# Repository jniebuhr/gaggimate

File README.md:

<p align="center">

<br />

[![CC BY-NC-SA 4.0][cc-by-nc-sa-shield]][cc-by-nc-sa]
[![Sonar QG][sonar-shield]][sonar-url]
[![Sonar Violations][sonar-violations]][sonar-url]
[![Sonar Tech Debt][sonar-tech-debt]][sonar-url]

</p>

This project upgrades a Gaggia espresso machine with smart controls to improve your coffee-making experience. By adding a display and custom electronics, you can monitor and control the machine more easily.

## Features

- **Temperature Control**: Monitor the boiler temperature to ensure optimal brewing conditions.
- **Brew timer**: Set a target duration and run the brewing for the specific time.
- **Steam and Hot Water mode**: Control the pump and valve to run the respective task.
- **Safety Features**: Automatic shutoff if the system becomes unresponsive or overheats.
- **User Interface**: Simple, intuitive display to control and monitor the machine.

## Screenshots and Images

### How to buy

You can buy your kit on https://shop.gaggimate.eu/

## How It Works

The display allows you to control the espresso machine and see live temperature updates. If the machine becomes unresponsive or the temperature goes too high, it will automatically turn off for safety.

## Docs

The docs were moved to [https://gaggimate.eu/](https://gaggimate.eu/). You can find all sourcing and assembly information there.
Additional documentation for the WebSocket API can be found in [docs/websocket-api.yaml](docs/websocket-api.yaml).

## Hardware Files

The hardware files were moved to [gaggimate/parts](https://github.com/gaggimate/parts).

## License

This work is licensed under CC BY-NC-SA 4.0. To view a copy of this license, visit https://creativecommons.org/licenses/by-nc-sa/4.0/

[sonar-violations]: https://img.shields.io/sonar/blocker_violations/jniebuhr_gaggimate?server=https%3A%2F%2Fsonarcloud.io&style=for-the-badge
[sonar-shield]: https://img.shields.io/sonar/quality_gate/jniebuhr_gaggimate?server=https%3A%2F%2Fsonarcloud.io&style=for-the-badge
[sonar-tech-debt]: https://img.shields.io/sonar/tech_debt/jniebuhr_gaggimate?server=https%3A%2F%2Fsonarcloud.io&style=for-the-badge
[sonar-url]: https://sonarcloud.io/project/overview?id=jniebuhr_gaggimate
[cc-by-nc-sa]: http://creativecommons.org/licenses/by-nc-sa/4.0/
[cc-by-nc-sa-image]: https://licensebuttons.net/l/by-nc-sa/4.0/88x31.png
[cc-by-nc-sa-shield]: https://img.shields.io/badge/License-CC%20BY--NC--SA%204.0-lightgrey.svg?style=for-the-badge

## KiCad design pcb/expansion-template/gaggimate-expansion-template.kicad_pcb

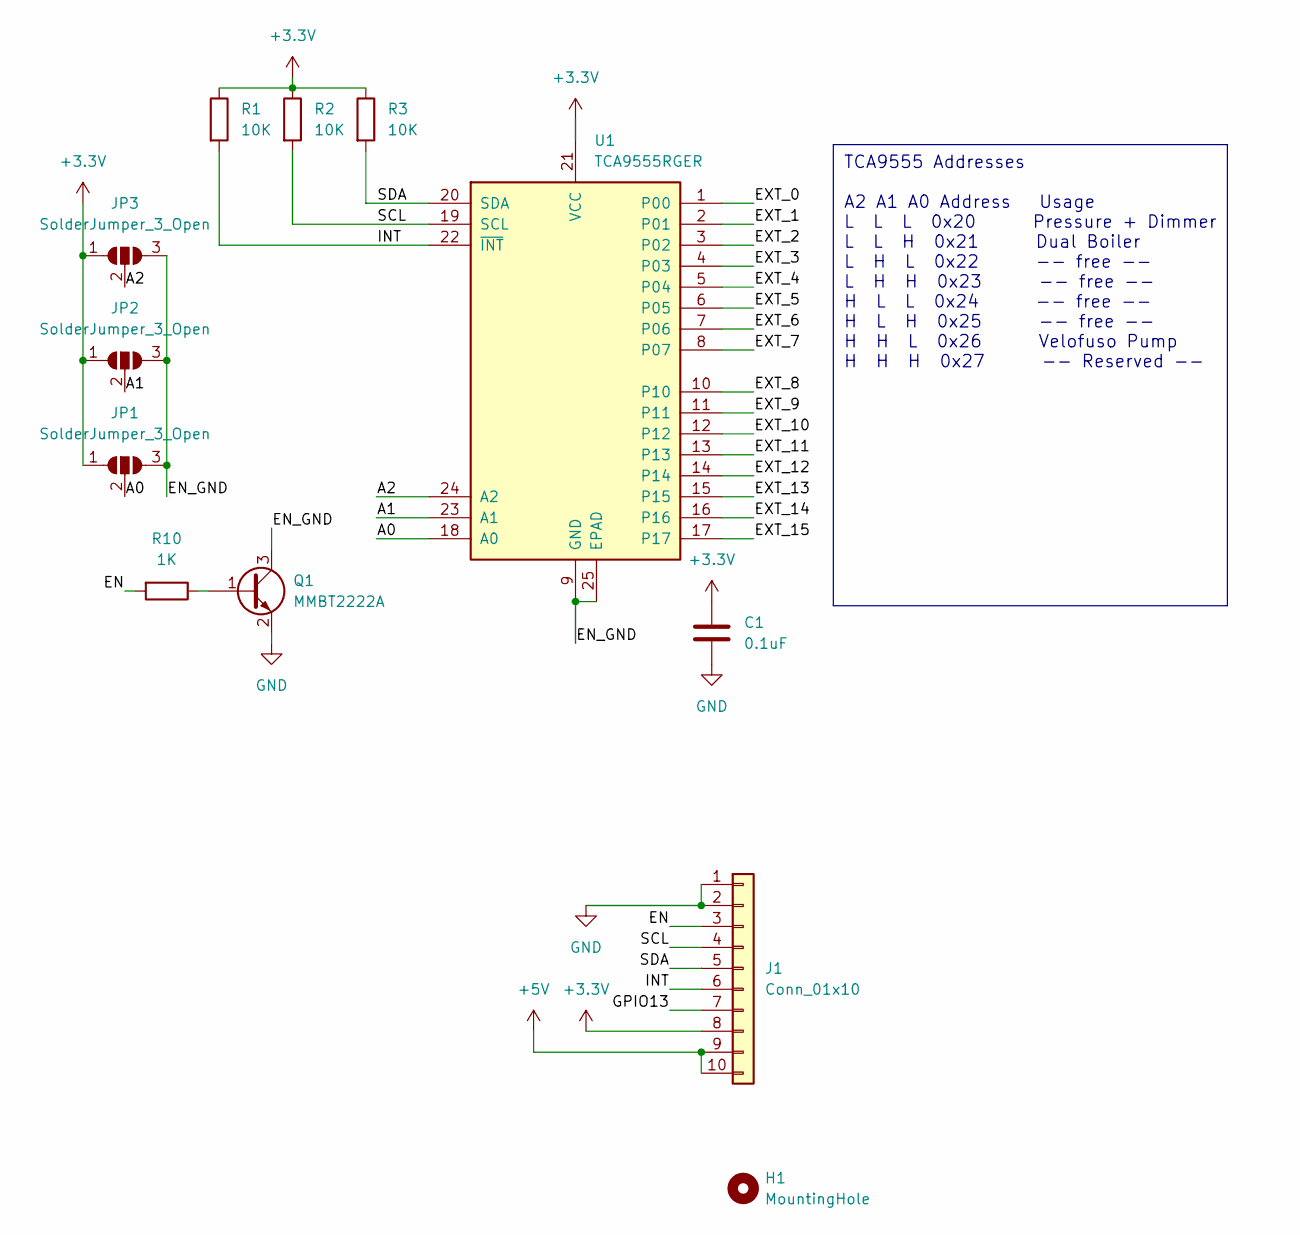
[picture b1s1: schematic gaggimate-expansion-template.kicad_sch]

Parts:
C1: 0.1uF; C_0603_1608Metric
H1: MountingHole; MountingHole_2.7mm_M2.5
J1: Conn_01x10; PinSocket_1x10_P2.54mm_Vertical
JP1, JP2, JP3: SolderJumper_3_Open; SolderJumper-3_P1.3mm_Open_RoundedPad1.0x1.5mm
Q1: MMBT2222A; SOT-23
R1, R2, R3: 10K; R_0603_1608Metric
R10: 1K; R_0603_1608Metric
U1: TCA9555RGER; VQFN-24-1EP_4x4mm_P0.5mm_EP2.45x2.45mm

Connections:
+3.3V: C1.1, J1.8, JP1.1 (A), JP2.1 (A), JP3.1 (A), R1.1, R2.1, R3.1, U1.21 (VCC)
+5V: J1.9, J1.10
/A0: JP1.2 (C), U1.18 (A0)
/A1: JP2.2 (C), U1.23 (A1)
/A2: JP3.2 (C), U1.24 (A2)
/EN: J1.3, R10.2
/EN_GND: JP1.3 (B), JP2.3 (B), JP3.3 (B), Q1.3 (C), U1.9 (GND), U1.25 (EPAD)
/EXT_0: U1.1 (P00)
/EXT_1: U1.2 (P01)
/EXT_2: U1.3 (P02)
/EXT_3: U1.4 (P03)
/EXT_4: U1.5 (P04)
/EXT_5: U1.6 (P05)
/EXT_6: U1.7 (P06)
/EXT_7: U1.8 (P07)
/EXT_8: U1.10
/EXT_9: U1.11
/EXT_10: U1.12
/EXT_11: U1.13
/EXT_12: U1.14
/EXT_13: U1.15
/EXT_14: U1.16
/EXT_15: U1.17
/GPIO13: J1.7
/INT: J1.6, R1.2, U1.22 (~INT)
/SCL: J1.4, R2.2, U1.19 (SCL)
/SDA: J1.5, R3.2, U1.20 (SDA)
GND: C1.2, J1.1, J1.2, Q1.2 (E)
unnamed: Q1.1 (B), R10.1

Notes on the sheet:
TCA9555 Addresses A2 A1 A0 Address Usage L L L 0x20 Pressure + Dimmer L L H 0x21 Dual Boiler L H L 0x22 -- free -- L H H 0x23 -- free -- H L L 0x24 -- free -- H L H 0x25 -- free -- H H L 0x26 Velofuso Pump H H H 0x27 -- Reserved --

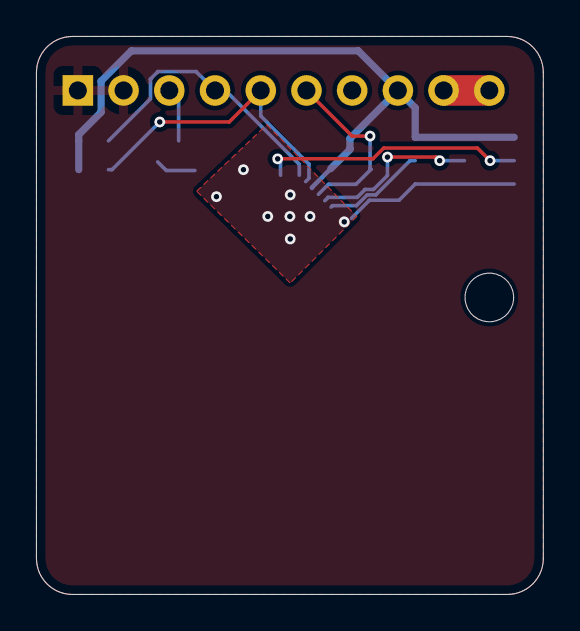
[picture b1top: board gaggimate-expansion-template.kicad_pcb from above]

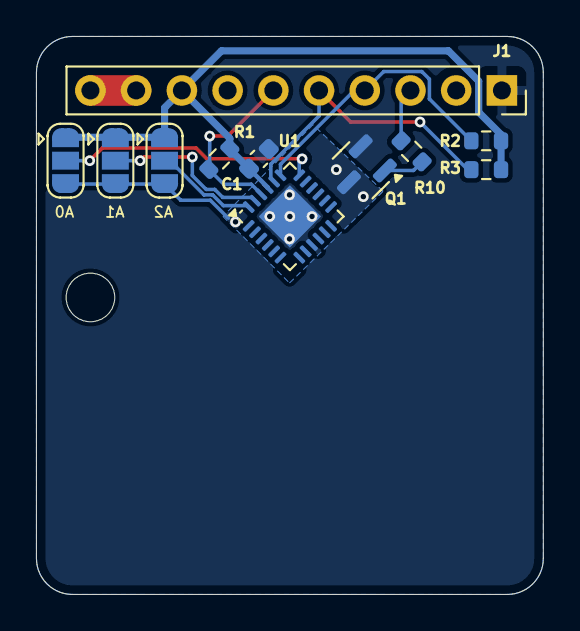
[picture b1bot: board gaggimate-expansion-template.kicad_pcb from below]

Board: 2 copper layers, 28.2 x 31.0 mm, 12 parts (11 on the bottom side), 12 nets.

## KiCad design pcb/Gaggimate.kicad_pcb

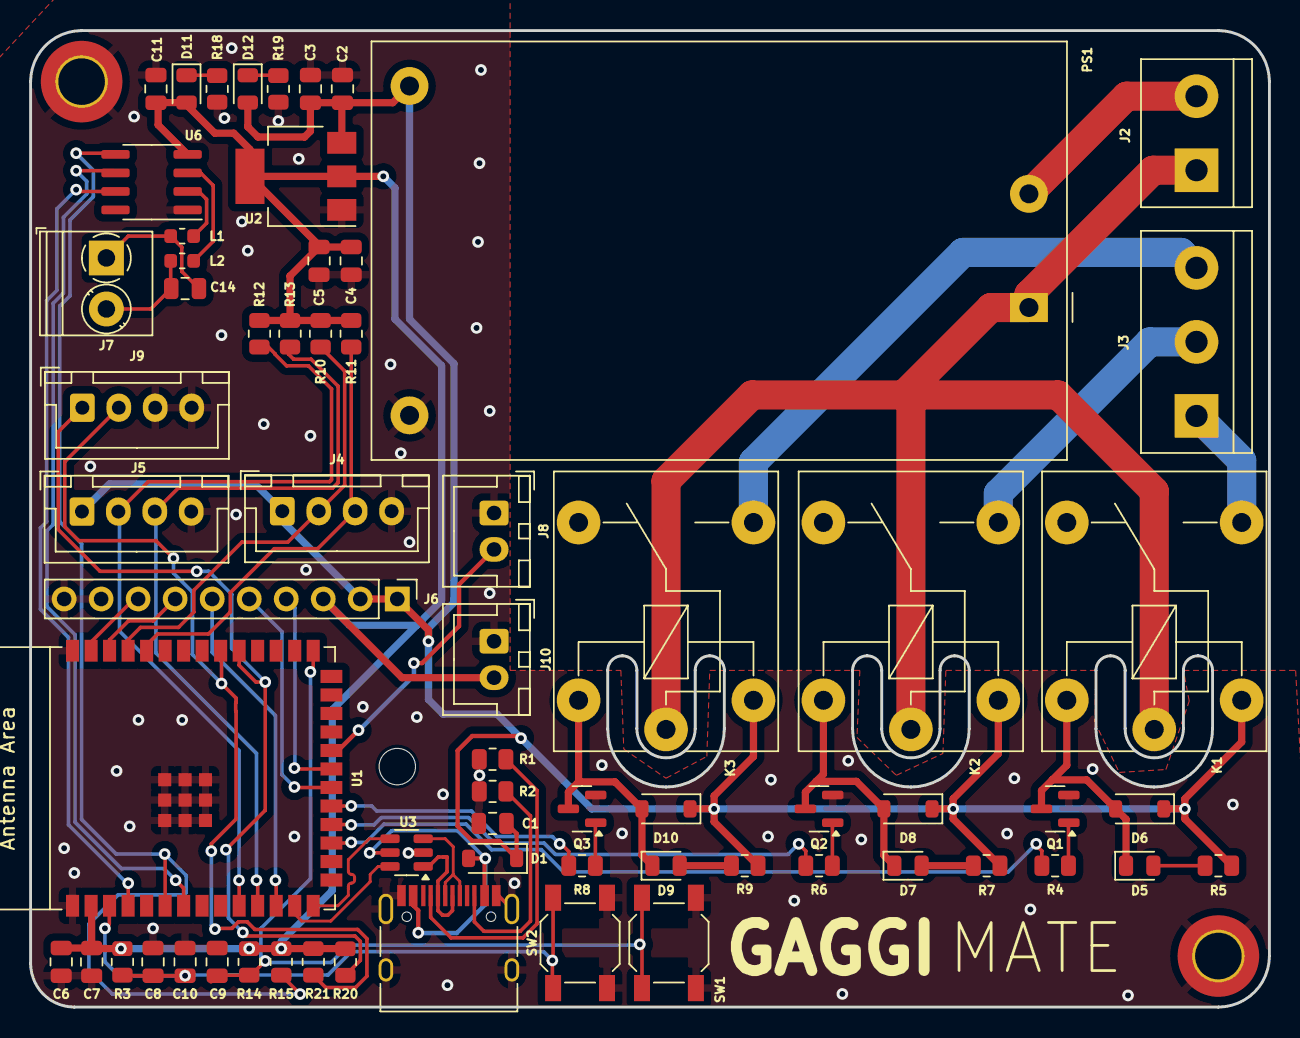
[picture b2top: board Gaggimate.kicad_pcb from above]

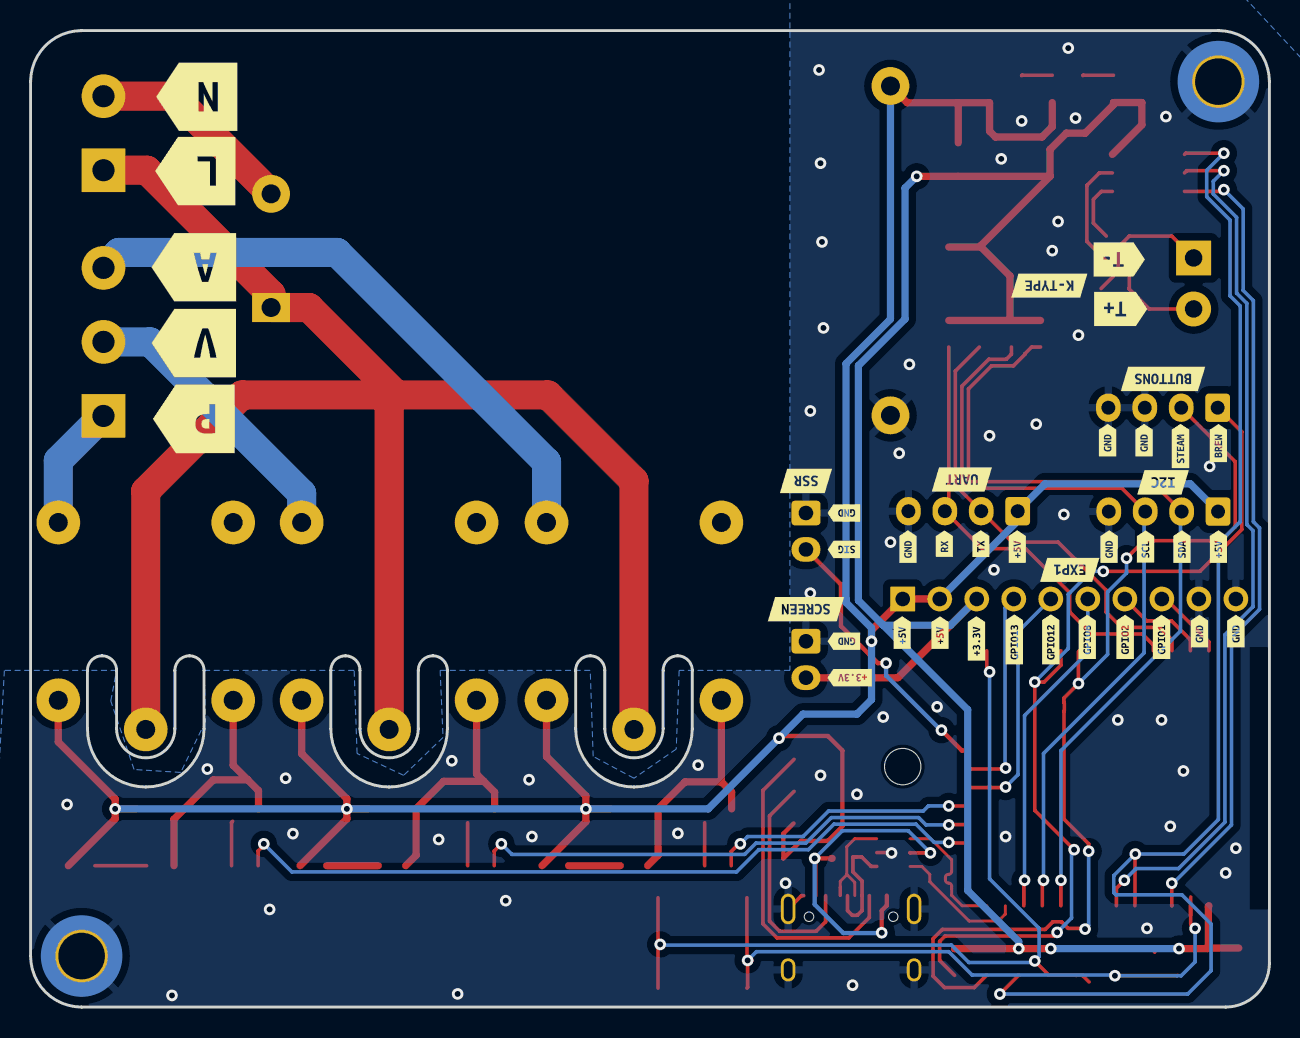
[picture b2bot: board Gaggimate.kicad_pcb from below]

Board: 2 copper layers, 85.0 x 67.0 mm, 107 parts (40 on the bottom side), 50 nets.

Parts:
C1, C2, C6: 10uF; C_0805_2012Metric
C3, C5, C7, C9, C10: 0.1uF; C_0805_2012Metric
C4: 22uF; C_0805_2012Metric
C8, C11: 1uF; C_0805_2012Metric
C14: 10nF; C_0805_2012Metric
D1: 1N5819; D_SOD-123
D5, D7, D9, D11, D12: LED; LED_0805_2012Metric
D6, D8, D10: 1N4148W; D_SOD-123
H1, H1#2: MountingHole_Pad; MountingHole_3.2mm_M3_DIN965_Pad_TopBottom
J1: USB_C_Receptacle; USB_C_Receptacle_HRO_TYPE-C-31-M-12
J2: Conn_01x02; TerminalBlock_bornier-2_P5.08mm
J3: Conn_01x03; TerminalBlock_bornier-3_P5.08mm
J4, J5, J9: Conn_01x04; JST_XH_B4B-XH-A_1x04_P2.50mm_Vertical
J6: Conn_01x10; PinHeader_1x10_P2.54mm_Vertical
J7: Conn_01x02; TerminalBlock_Phoenix_PT-1,5-2-3.5-H_1x02_P3.50mm_Horizontal
J8, J10: Conn_01x02; JST_XH_B2B-XH-A_1x02_P2.50mm_Vertical
K1, K2, K3: Relay_SPDT; Relay_SPDT_Finder_36.11
L1, L2: 470R; L_0603_1608Metric
PS1: HLK-10M05; Converter_ACDC_HiLink_HLK-10Mxx
Q1, Q2, Q3: MMBT2222A; SOT-23
R1, R2: 5.1K; R_0805_2012Metric
R3, R10, R11, R12, R13, R14, R15, R20, R21: 10K; R_0805_2012Metric
R4, R6, R8: 1K; R_0805_2012Metric
R5, R7, R9, R19: 150R; R_0805_2012Metric
R18: 68R; R_0805_2012Metric
SW1, SW2: SW_Push; SW_SPST_SKQG_WithStem
U1: ESP32-S3-WROOM-1
U2: AMS1117-3.3; SOT-223-3_TabPin2
U3: USBLC6-2SC6; SOT-23-6
U6: MAX31855EASA; SOIC-8_3.9x4.9mm_P1.27mm
kibuzzard-6735A9F6: G***; kibuzzard-6735A9F6
kibuzzard-6735A9FB: G***; kibuzzard-6735A9FB
kibuzzard-67411A55: G***; kibuzzard-67411A55
kibuzzard-673226A0: G***; kibuzzard-673226A0
kibuzzard-673226A8: G***; kibuzzard-673226A8
kibuzzard-673226AF, kibuzzard-673226AF#2: G***; kibuzzard-673226AF
kibuzzard-673226B7: G***; kibuzzard-673226B7
kibuzzard-673226BE: G***; kibuzzard-673226BE
kibuzzard-673226D2: G***; kibuzzard-673226D2
kibuzzard-6732257B: G***; kibuzzard-6732257B
kibuzzard-6732261A: G***; kibuzzard-6732261A
kibuzzard-6732266F: G***; kibuzzard-6732266F
kibuzzard-6732270D: G***; kibuzzard-6732270D
kibuzzard-6732274F: G***; kibuzzard-6732274F
kibuzzard-6732277B: G***; kibuzzard-6732277B
kibuzzard-6732278E: G***; kibuzzard-6732278E
kibuzzard-6732279D: G***; kibuzzard-6732279D
kibuzzard-67322575: G***; kibuzzard-67322575
kibuzzard-67322649, kibuzzard-67322649#2, kibuzzard-67322649#3, kibuzzard-67322649#4, kibuzzard-67322649#5, kibuzzard-67322649#6, kibuzzard-67322649#7, kibuzzard-67322649#8: G***; kibuzzard-67322649
kibuzzard-67322650, kibuzzard-67322650#2, kibuzzard-67322650#3, kibuzzard-67322650#4: G***; kibuzzard-67322650
kibuzzard-67322655: G***; kibuzzard-67322655
kibuzzard-67322681: G***; kibuzzard-67322681
kibuzzard-67322686: G***; kibuzzard-67322686
kibuzzard-67322714: G***; kibuzzard-67322714
kibuzzard-67322749: G***; kibuzzard-67322749
kibuzzard-67322755: G***; kibuzzard-67322755
kibuzzard-67322768: G***; kibuzzard-67322768
kibuzzard-67322783: G***; kibuzzard-67322783
kibuzzard-67322833: G***; kibuzzard-67322833

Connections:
+3.3V: C4.1, C5.1, C6.1, C7.1, C11.1, D11.2 (A), J6.3, J10.2, R3.1, R10.1, R11.1, R12.1, R13.1, R14.1, R15.1, R20.1, R21.1, U1.2 (3V3), U2.2 (VO), U6.4 (V_CC)
+5V: C1.1, C2.1, C3.1, D1.1 (K), D6.1 (K), D8.1 (K), D10.1 (K), D12.2 (A), J4.1, J5.1, J6.1, J6.2, K1.A1, K2.A1, K3.A1, PS1.4 (+Vout), R5.2, R7.2, R9.2, U2.3 (VI)
/BOOT: C9.1, R14.2, SW1.2, U1.27 (GPIO0/BOOT)
/BTN_BREW: J9.1, R20.2, U1.31 (GPIO38/FSPIWP/SUBSPIWP)
/BTN_STEAM: J9.2, R21.2, U1.32 (MTCK/GPIO39/CLK_OUT3/SUBSPICS1)
/CHIP_PU: C8.1, C10.1, R3.2, SW2.2, U1.3 (EN)
/GPIO1: J6.8, U1.39 (GPIO1/TOUCH1/ADC1_CH0)
/GPIO2: J6.7, U1.38 (GPIO2/TOUCH2/ADC1_CH1)
/GPIO8: J6.6, U1.12 (GPIO8/TOUCH8/ADC1_CH7/SUBSPICS1)
/GPIO12: J6.5, U1.20 (GPIO12/TOUCH12/ADC2_CH1/FSPICLK/FSPIIO6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)
/GPIO13: J6.4, U1.21 (GPIO13/TOUCH13/ADC2_CH2/FSPIQ/FSPIIO7/S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)
/LINE_GRINDER: J3.3, K3.14
/LINE_PUMP: J3.1, K1.14
/LINE_VALVE: J3.2, K2.14
/MAX_CS: U1.7 (GPIO7/TOUCH7/ADC1_CH6), U6.6 (~CS)
/RELAY_GRINDER: R8.2, U1.19 (GPIO11/TOUCH11/ADC2_CH0/FSPID/FSPIIO5/S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)
/RELAY_PUMP: R4.2, U1.17 (GPIO9/TOUCH9/ADC1_CH8/FSPIHD/SUBSPIHD)
/RELAY_VALVE: R6.2, U1.18 (GPIO10/TOUCH10/ADC1_CH9/FSPICS0/FSPIIO4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)
/SCL: J5.2, R12.2, U1.10 (GPIO17/U1TXD/ADC2_CH6)
/SDA: J5.3, R13.2, U1.11 (GPIO18/U1RXD/ADC2_CH7/CLK_OUT3)
/SPI_CLK: R15.2, U1.6 (GPIO6/TOUCH6/ADC1_CH5), U6.5 (SCK)
/SPI_MISO: U1.4 (GPIO4/TOUCH4/ADC1_CH3), U6.7 (SO)
/SSR: J8.2, U1.22 (GPIO14/TOUCH14/ADC2_CH3/FSPIWP/FSPIDQS/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)
/UART_RX0: J4.3, R11.2, U1.36 (U0RXD/GPIO44/CLK_OUT2)
/UART_TX0: J4.2, R10.2, U1.37 (U0TXD/GPIO43/CLK_OUT1)
/USB_DN: U1.13 (GPIO19/U1RTS/ADC2_CH8/CLK_OUT2/USB_D-), U3.6 (I/O1)
/USB_DP: U1.14 (GPIO20/U1CTS/ADC2_CH9/CLK_OUT1/USB_D+), U3.4 (I/O2)
/USB_UF_DN: J1.A7 (D-), J1.B7 (D-), U3.1 (I/O1)
/USB_UF_DP: J1.A6 (D+), J1.B6 (D+), U3.3 (I/O2)
GND: C1.2, C2.2, C3.2, C4.2, C5.2, C6.2, C7.2, C8.2, C9.2, C10.2, C11.2, H1.1, H1#2.1, J1.A1 (GND), J1.A12 (GND), J1.B1 (GND), J1.B12 (GND), J1.S1 (SHIELD), J4.4, J5.4, J6.9, J6.10, J8.1, J9.3, J9.4, J10.1, PS1.3 (-Vout), Q1.2 (E), Q2.2 (E), Q3.2 (E), R1.1, R2.1, R18.2, R19.2, SW1.1, SW2.1, U1.1 (GND), U1.40 (GND), U1.41 (GND), U2.1 (GND), U3.2 (GND), U6.1 (GND)
LINE: J2.1, K1.11, K2.11, K3.11, PS1.1 (AC/L)
NEUT: J2.2, PS1.2 (AC/N)
unnamed: D1.2 (A), J1.A4 (VBUS), J1.A9 (VBUS), J1.B4 (VBUS), J1.B9 (VBUS), U3.5 (VBUS)
unnamed: D5.2 (A), R5.1
unnamed: D5.1 (K), D6.2 (A), K1.A2, Q1.3 (C)
unnamed: D7.2 (A), R7.1
unnamed: D7.1 (K), D8.2 (A), K2.A2, Q2.3 (C)
unnamed: D9.2 (A), R9.1
unnamed: D9.1 (K), D10.2 (A), K3.A2, Q3.3 (C)
unnamed: D11.1 (K), R18.1
unnamed: D12.1 (K), R19.1
unnamed: J1.A5 (CC1), R1.2
unnamed: J1.B5 (CC2), R2.2
unnamed: C14.2, J7.1, L1.1
unnamed: C14.1, J7.2, L2.1
unnamed: Q1.1 (B), R4.1
unnamed: Q2.1 (B), R6.1
unnamed: Q3.1 (B), R8.1
unnamed: L2.2, U6.3 (T+)
unnamed: L1.2, U6.2 (T-)
